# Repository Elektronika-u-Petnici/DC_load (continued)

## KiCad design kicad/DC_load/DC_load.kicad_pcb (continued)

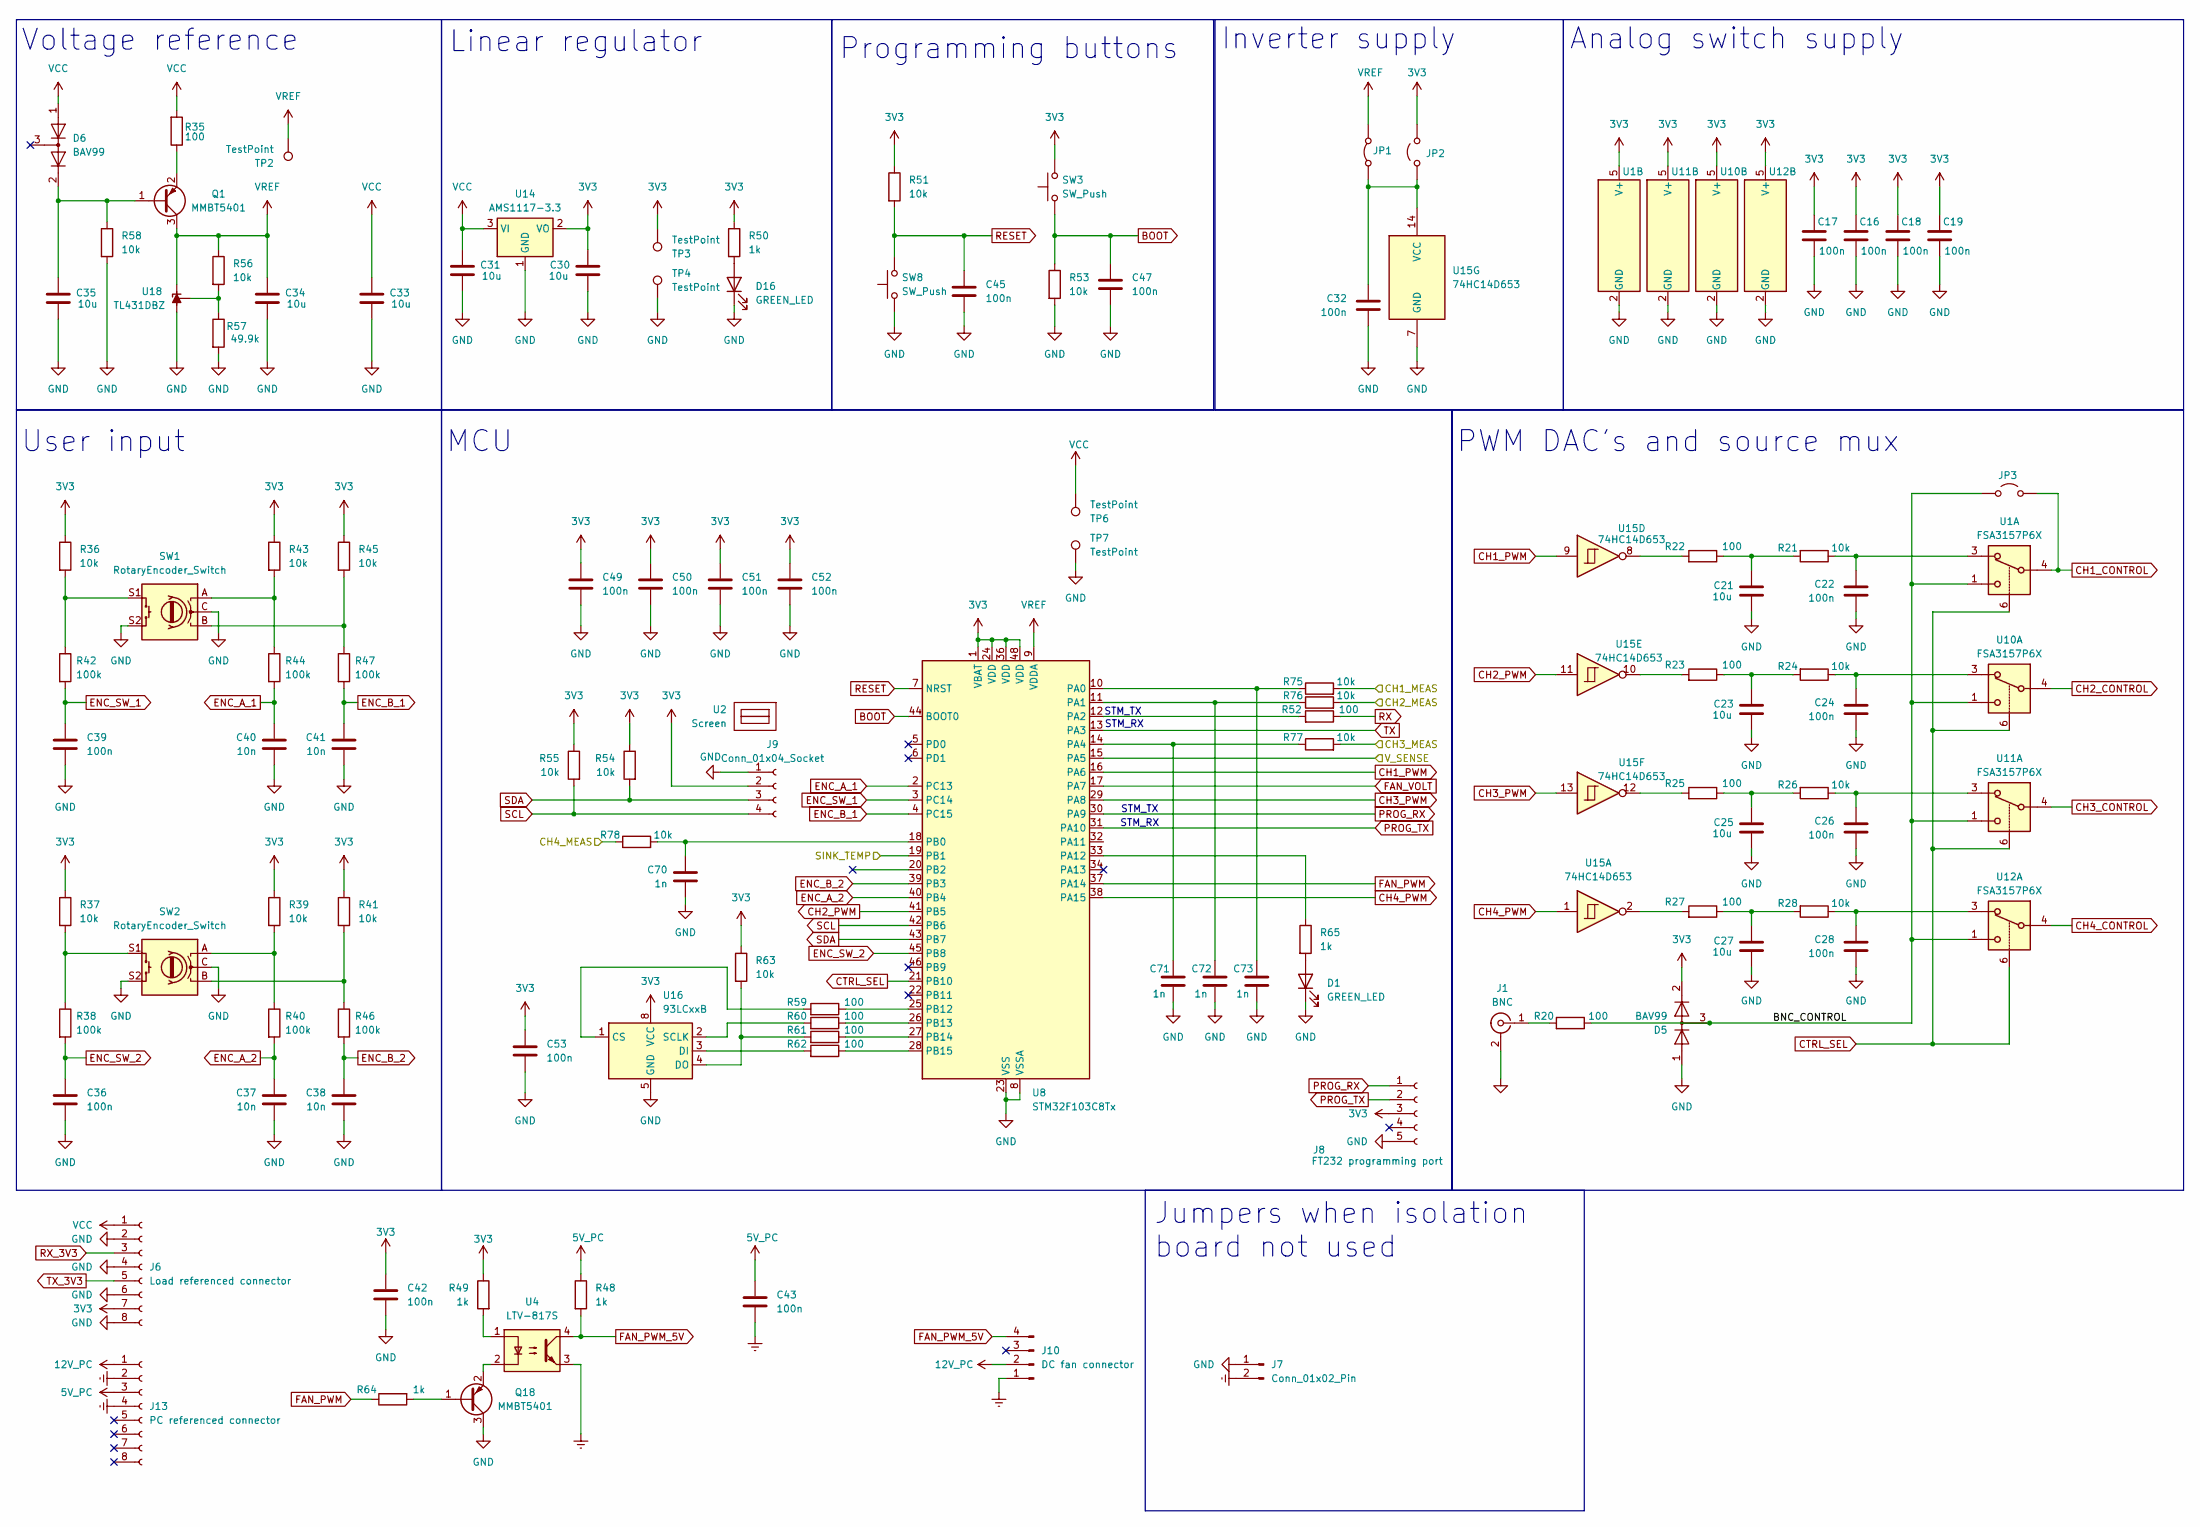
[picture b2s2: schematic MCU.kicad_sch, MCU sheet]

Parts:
C16, C17, C18, C19, C22, C24, C26, C28, C32, C36, C39, C42, C43, C45, C47, C49, C50, C51, C52, C53: 100n; C_0603_1608Metric_Pad1.08x0.95mm_HandSolder; LCSC C14663
C21, C23, C25, C27, C30, C31, C33, C34, C35: 10u; C_0603_1608Metric_Pad1.08x0.95mm_HandSolder; LCSC C96446
C37, C38, C40, C41: 10n; C_0603_1608Metric_Pad1.08x0.95mm_HandSolder; LCSC C57112
C70, C71, C72, C73: 1n; C_0603_1608Metric_Pad1.08x0.95mm_HandSolder; LCSC C1588
D1, D16: GREEN_LED; LED_0805_2012Metric_Pad1.15x1.40mm_HandSolder; LCSC C2297
D5, D6: BAV99; SOT-23; LCSC C2500
J1: BNC; BNC_Amphenol_B6252HB-NPP3G-50_Horizontal
J6: Load referenced connector; PinHeader_1x08_P2.54mm_Vertical
J7: Conn_01x02_Pin; PinHeader_1x02_P2.54mm_Vertical
J8: FT232 programming port; PinSocket_1x05_P2.54mm_Vertical
J9: Conn_01x04_Socket; PinSocket_1x04_P2.54mm_Vertical
J10: DC fan connector; PinHeader_1x04_P2.54mm_Vertical
J13: PC referenced connector; PinHeader_1x08_P2.54mm_Vertical
JP1: Jumper_2_Bridged; SolderJumper-2_P1.3mm_Bridged_RoundedPad1.0x1.5mm
JP2, JP3: Jumper_2_Open; SolderJumper-2_P1.3mm_Open_RoundedPad1.0x1.5mm
Q1, Q18: MMBT5401; SOT-23; LCSC C8326
R20, R22, R23, R25, R27, R35, R52, R59, R60, R61, R62: 100; R_0603_1608Metric_Pad0.98x0.95mm_HandSolder; LCSC C22775
R21, R24, R26, R28, R36, R37, R39, R41, R43, R45, R51, R53, R54, R55, R56, R58, R63, R75, R76, R77, R78: 10k; R_0603_1608Metric_Pad0.98x0.95mm_HandSolder; LCSC C25804
R38, R40, R42, R44, R46, R47: 100k; R_0603_1608Metric_Pad0.98x0.95mm_HandSolder; LCSC C25803
R48, R49, R64: 1k; R_0603_1608Metric_Pad0.98x0.95mm_HandSolder; LCSC C22962
R50, R65: 1k; R_0603_1608Metric_Pad0.98x0.95mm_HandSolder; LCSC C21190
R57: 49.9k; R_0603_1608Metric_Pad0.98x0.95mm_HandSolder; LCSC C23184
SW1, SW2: RotaryEncoder_Switch; RotaryEncoder_Alps_EC11E-Switch_Vertical_H20mm
SW3, SW8: SW_Push; TS-1088-AR02016; LCSC C720477
TP2, TP3, TP4, TP6, TP7: TestPoint; TestPoint_Pad_D2.0mm
U1, U10, U11, U12: FSA3157P6X; SOT-363_SC-70-6_Handsoldering
U2: Screen; WC1602A - below
U4: LTV-817S; SMDIP-4_W9.53mm
U8: STM32F103C8Tx; LQFP-48_7x7mm_P0.5mm
U14: AMS1117-3.3; SOT-223-3_TabPin2; LCSC C6186
U15: 74HC14D653; SOIC-14_3.9x8.7mm_P1.27mm; LCSC C5605
U16: 93LCxxB; SOIC-8_3.9x4.9mm_P1.27mm
U18: TL431DBZ; SOT-23; LCSC C3113

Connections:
3V3: C16.2, C17.2, C18.2, C19.2, C30.1, C42.2, C49.2, C50.2, C51.2, C52.2, C53.2, D5.2 (A), J6.7, J8.3, J9.2, JP2.2 (B), R36.1, R37.1, R39.1, R41.1, R43.1, R45.1, R49.1, R50.1, R51.1, R54.1, R55.1, R63.1, SW3.2, TP3.1, U1.5 (V+), U8.1 (VBAT), U8.24 (VDD), U8.36 (VDD), U8.48 (VDD), U10.5 (V+), U11.5 (V+), U12.5 (V+), U14.2 (VO), U16.8 (VCC); also elsewhere on the board
5V_PC: C43.2, J13.3, R48.1
12V_PC: J10.2, J13.1
/Microcontroller/BNC_CONTROL: D5.3 (K), JP3.1 (A), R20.1, U1.1, U10.1, U11.1, U12.1
/Microcontroller/CH1_MEAS: R75.2; also elsewhere on the board
/Microcontroller/CH2_MEAS: R76.2; also elsewhere on the board
/Microcontroller/CH3_MEAS: R77.2; also elsewhere on the board
/Microcontroller/CH4_MEAS: R78.1; also elsewhere on the board
/Microcontroller/SINK_TEMP: U8.19 (PB1); also elsewhere on the board
/Microcontroller/V_SENSE: U8.15 (PA5); also elsewhere on the board
BOOT: C47.2, R53.1, SW3.1, U8.44 (BOOT0)
CH1_CONTROL: JP3.2 (B), U1.4; also elsewhere on the board
CH1_PWM: U8.16 (PA6), U15.9
CH2_CONTROL: U10.4; also elsewhere on the board
CH2_PWM: U8.41 (PB5), U15.11
CH3_CONTROL: U11.4; also elsewhere on the board
CH3_PWM: U8.29 (PA8), U15.13
CH4_CONTROL: U12.4; also elsewhere on the board
CH4_PWM: U8.38 (PA15), U15.1
CTRL_SEL: U1.6, U8.21 (PB10), U10.6, U11.6, U12.6
ENC_A_1: C40.2, R44.2, U8.2 (PC13)
ENC_A_2: C37.2, R40.2, U8.40 (PB4)
ENC_B_1: C41.2, R47.2, U8.4 (PC15)
ENC_B_2: C38.2, R46.2, U8.39 (PB3)
ENC_SW_1: C39.2, R42.2, U8.3 (PC14)
ENC_SW_2: C36.2, R38.2, U8.45 (PB8)
Earth: C43.1, J7.2, J10.1, J13.2, J13.4, U4.3
FAN_PWM: R64.1, U8.37 (PA14)
FAN_PWM_5V: J10.4, R48.2, U4.4
FAN_VOLT: U8.17 (PA7)
GND: C16.1, C17.1, C18.1, C19.1, C21.2, C22.1, C23.2, C24.1, C25.2, C26.1, C27.2, C28.1, C30.2, C31.2, C32.1, C33.2, C34.2, C35.2, C36.1, C37.1, C38.1, C39.1, C40.1, C41.1, C42.1, C45.1, C47.1, C49.1, C50.1, C51.1, C52.1, C53.1, C70.1, C71.1, C72.1, C73.1, D1.1 (K), D5.1 (K), D16.1 (K), J1.2 (Ext), J6.2, J6.4, J6.6, J6.8, J7.1, J8.5, J9.1, Q18.3 (C), R53.2, R57.2, R58.2, SW1.C, SW1.S2, SW2.C, SW2.S2, SW8.1, TP4.1, TP7.1, U1.2 (GND), U8.8 (VSSA), U8.23 (VSS), U8.35 (VSS), U8.47 (VSS), U10.2 (GND), U11.2 (GND), U12.2 (GND), U14.1 (GND), U15.7 (GND), U16.5 (GND), U18.3 (A); also elsewhere on the board
unnamed: C21.1, R21.2, R22.1
unnamed: C22.2, R21.1, U1.3
unnamed: C23.1, R23.1, R24.2
unnamed: C24.2, R24.1, U10.3
unnamed: C25.1, R25.1, R26.2
unnamed: C26.2, R26.1, U11.3
unnamed: C27.1, R27.1, R28.2
unnamed: C28.2, R28.1, U12.3
unnamed: D1.2 (A), R65.2
unnamed: C35.1, D6.2 (A), Q1.1 (B), R58.1
unnamed: D16.2 (A), R50.2
unnamed: J1.1 (In), R20.2
unnamed: C32.2, JP1.1 (A), JP2.1 (A), U15.14 (VCC)
unnamed: Q1.2 (E), R35.1
unnamed: Q18.1 (B), R64.2
unnamed: Q18.2 (E), U4.2
unnamed: R22.2, U15.8
unnamed: R23.2, U15.10
unnamed: R25.2, U15.12
unnamed: R27.2, U15.2
unnamed: R36.2, R42.1, SW1.S1
unnamed: R37.2, R38.1, SW2.S1
unnamed: R39.2, R40.1, SW2.A
unnamed: R41.2, R46.1, SW2.B
unnamed: R43.2, R44.1, SW1.A
unnamed: R45.2, R47.1, SW1.B
unnamed: R49.2, U4.1
unnamed: C73.2, R75.1, U8.10 (PA0)
unnamed: C72.2, R76.1, U8.11 (PA1)
unnamed: R52.2, U8.12 (PA2)
unnamed: C71.2, R77.1, U8.14 (PA4)
unnamed: R65.1, U8.33 (PA12)
unnamed: C70.2, R78.2, U8.18 (PB0)
unnamed: R59.1, U8.25 (PB12)
unnamed: R60.1, U8.26 (PB13)
unnamed: R61.1, U8.27 (PB14)
unnamed: R62.1, U8.28 (PB15)
unnamed: R59.2, U16.1 (CS)
unnamed: R62.2, U16.3 (DI)
unnamed: R61.2, R63.2, U16.4 (DO)
unnamed: R60.2, U16.2 (SCLK)
unnamed: R56.2, R57.1, U18.2 (REF)
PROG_RX: J8.1, U8.30 (PA9)
PROG_TX: J8.2, U8.31 (PA10)
RESET: C45.2, R51.2, SW8.2, U8.7 (NRST)
RX: R52.1
RX_3V3: J6.3
SCL: J9.4, R55.2, U8.42 (PB6)
SDA: J9.3, R54.2, U8.43 (PB7)
TX: U8.13 (PA3)
TX_3V3: J6.5
VCC: C31.1, C33.1, D6.1 (K), J6.1, R35.2, TP6.1, U14.3 (VI); also elsewhere on the board
VREF: C34.1, JP1.2 (B), Q1.3 (C), R56.1, TP2.1, U8.9 (VDDA), U18.1 (K)

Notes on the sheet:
STM_RX
STM_TX
Programming buttons
Inverter supply
Jumpers when isolation board not used
PWM DAC's and source mux
Analog switch supply
MCU
Voltage reference
Linear regulator
User input

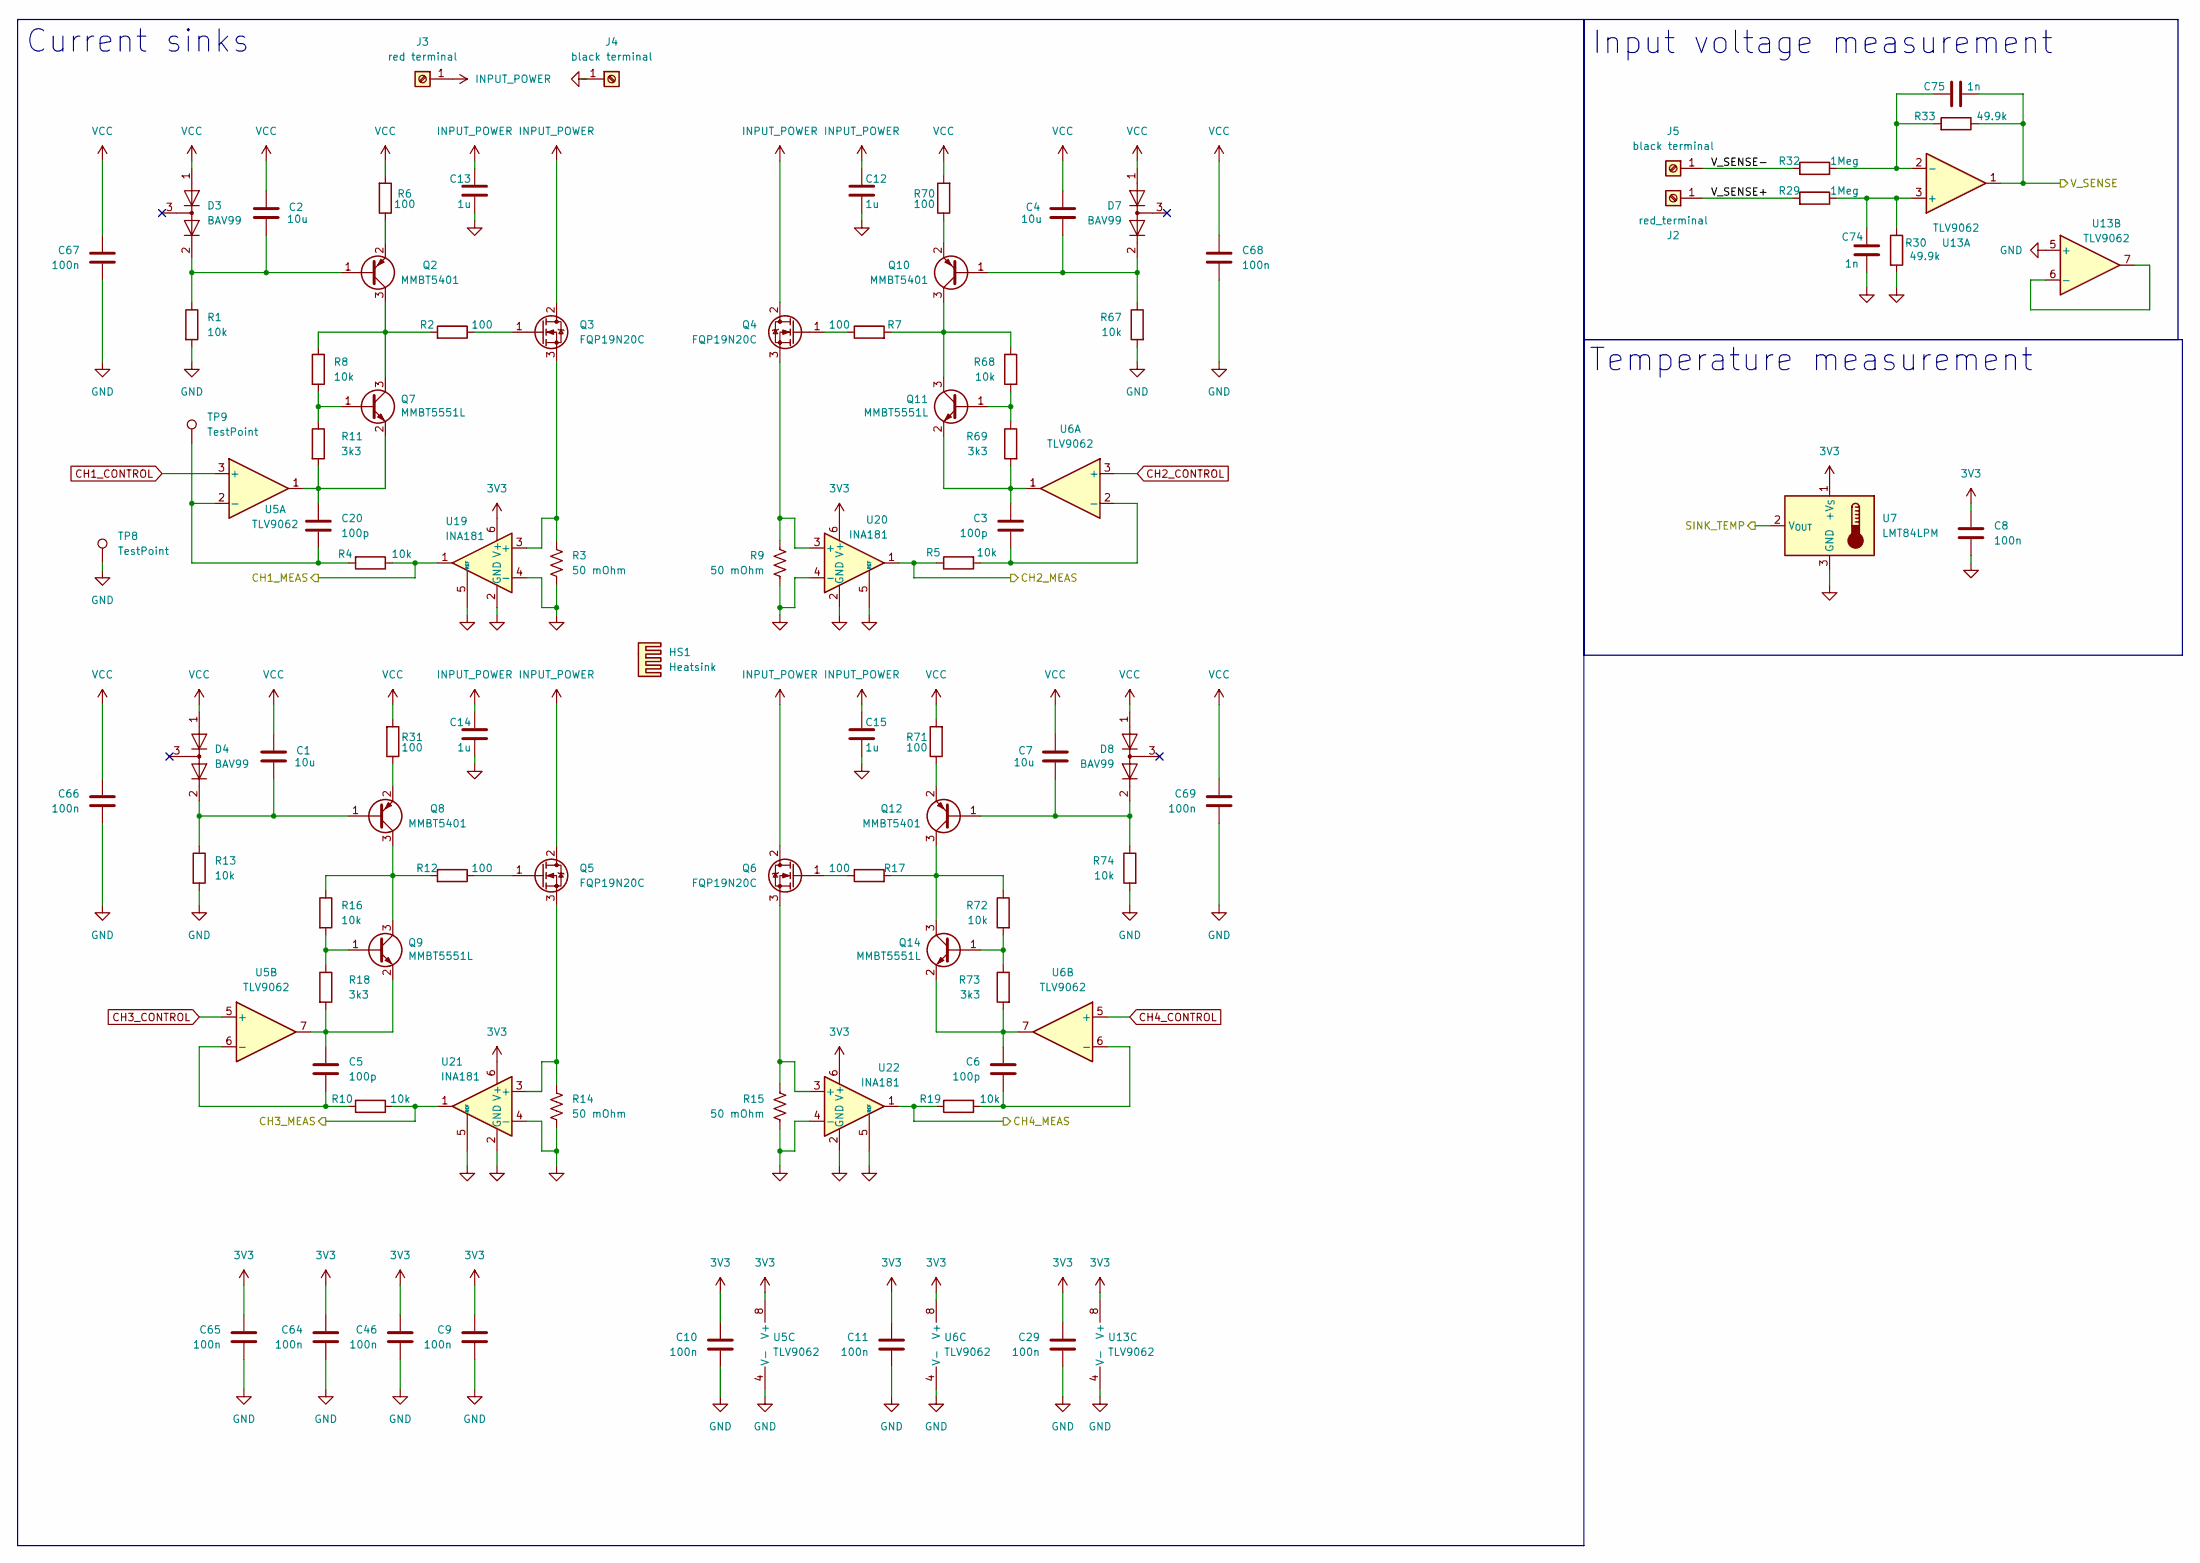
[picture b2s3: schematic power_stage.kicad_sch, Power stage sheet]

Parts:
C1, C2, C4, C7: 10u; C_0603_1608Metric_Pad1.08x0.95mm_HandSolder; LCSC C96446
C3, C5, C6, C20: 100p; C_0603_1608Metric_Pad1.08x0.95mm_HandSolder; LCSC C14858
C8: 100n; C_0603_1608Metric_Pad1.08x0.95mm_HandSolder
C9, C10, C11, C29, C46, C64, C65, C66, C67, C68, C69: 100n; C_0603_1608Metric_Pad1.08x0.95mm_HandSolder; LCSC C14663
C12, C13, C14, C15: 1u; C_2220_5750Metric_Pad1.97x5.40mm_HandSolder
C74, C75: 1n; C_0603_1608Metric_Pad1.08x0.95mm_HandSolder; LCSC C1588
D3, D4, D7, D8: BAV99; SOT-23; LCSC C2500
HS1: Heatsink; AMD_heatsink
J2: red_terminal; 4mm_terminal_red
J3: red terminal; 4mm_terminal_red
J4, J5: black terminal; 4mm_terminal_black
Q2, Q8, Q10, Q12: MMBT5401; SOT-23; LCSC C8326
Q3, Q4, Q5, Q6: FQP19N20C; TO-220-3_Horizontal_TabUp
Q7, Q9, Q11, Q14: MMBT5551L; SOT-23; LCSC C2145
R1, R4, R5, R8, R10, R13, R16, R19, R67, R68, R72, R74: 10k; R_0603_1608Metric_Pad0.98x0.95mm_HandSolder; LCSC C25804
R2, R6, R7, R12, R17, R31, R70, R71: 100; R_0603_1608Metric_Pad0.98x0.95mm_HandSolder; LCSC C22775
R3, R9, R14, R15: 50 mOhm; R_2512_6332Metric_Pad1.40x3.35mm_HandSolder
R11, R18, R69, R73: 3k3; R_0603_1608Metric_Pad0.98x0.95mm_HandSolder; LCSC C22978
R29, R32: 1Meg; R_0603_1608Metric_Pad0.98x0.95mm_HandSolder; LCSC C22935
R30, R33: 49.9k; R_0603_1608Metric_Pad0.98x0.95mm_HandSolder; LCSC C23184
TP8, TP9: TestPoint; TestPoint_Pad_D2.0mm
U5, U6, U13: TLV9062; SOIC-8_3.9x4.9mm_P1.27mm
U7: LMT84LPM; TO-92_Inline_W4.0mm_Horizontal_FlatSideUp
U19, U20, U21, U22: INA181; SOT-23-6

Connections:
3V3: C8.1, C9.2, C10.2, C11.2, C29.2, C46.2, C64.2, C65.2, U5.8 (V+), U6.8 (V+), U7.1 (+V_{S}), U13.8 (V+), U19.6 (V+), U20.6 (V+), U21.6 (V+), U22.6 (V+); also elsewhere on the board
/Microcontroller/CH1_MEAS: R4.1, U19.1; also elsewhere on the board
/Microcontroller/CH2_MEAS: R5.1, U20.1; also elsewhere on the board
/Microcontroller/CH3_MEAS: R10.1, U21.1; also elsewhere on the board
/Microcontroller/CH4_MEAS: R19.1, U22.1; also elsewhere on the board
/Microcontroller/SINK_TEMP: U7.2 (V_{OUT}); also elsewhere on the board
/Microcontroller/V_SENSE: C75.1, R33.1, U13.1; also elsewhere on the board
/Power_stage/V_SENSE+: J2.1, R29.2
/Power_stage/V_SENSE-: J5.1, R32.2
CH1_CONTROL: U5.3 (+); also elsewhere on the board
CH2_CONTROL: U6.3 (+); also elsewhere on the board
CH3_CONTROL: U5.5 (+); also elsewhere on the board
CH4_CONTROL: U6.5 (+); also elsewhere on the board
GND: C8.2, C9.1, C10.1, C11.1, C12.2, C13.2, C14.2, C15.2, C29.1, C46.1, C64.1, C65.1, C66.1, C67.1, C68.1, C69.1, C74.1, J4.1, R1.2, R3.2, R9.2, R13.2, R14.2, R15.2, R30.2, R67.2, R74.2, TP8.1, U5.4 (V-), U6.4 (V-), U7.3 (GND), U13.4 (V-), U13.5 (+), U19.2 (GND), U19.4 (-), U19.5 (REF), U20.2 (GND), U20.4 (-), U20.5 (REF), U21.2 (GND), U21.4 (-), U21.5 (REF), U22.2 (GND), U22.4 (-), U22.5 (REF); also elsewhere on the board
INPUT_POWER: C12.1, C13.1, C14.1, C15.1, J3.1, Q3.2 (D), Q4.2 (D), Q5.2 (D), Q6.2 (D)
unnamed: C2.2, D3.2 (A), Q2.1 (B), R1.1
unnamed: C1.2, D4.2 (A), Q8.1 (B), R13.1
unnamed: C4.2, D7.2 (A), Q10.1 (B), R67.1
unnamed: C7.2, D8.2 (A), Q12.1 (B), R74.1
unnamed: Q2.3 (C), Q7.3 (C), R2.2, R8.1
unnamed: Q2.2 (E), R6.1
unnamed: Q3.1 (G), R2.1
unnamed: Q3.3 (S), R3.1, U19.3 (+)
unnamed: Q4.1 (G), R7.1
unnamed: Q4.3 (S), R9.1, U20.3 (+)
unnamed: Q5.1 (G), R12.1
unnamed: Q5.3 (S), R14.1, U21.3 (+)
unnamed: Q6.1 (G), R17.1
unnamed: Q6.3 (S), R15.1, U22.3 (+)
unnamed: Q7.1 (B), R8.2, R11.1
unnamed: C20.2, Q7.2 (E), R11.2, U5.1
unnamed: Q8.3 (C), Q9.3 (C), R12.2, R16.1
unnamed: Q8.2 (E), R31.1
unnamed: Q9.1 (B), R16.2, R18.1
unnamed: C5.2, Q9.2 (E), R18.2, U5.7
unnamed: Q10.3 (C), Q11.3 (C), R7.2, R68.1
unnamed: Q10.2 (E), R70.1
unnamed: Q11.1 (B), R68.2, R69.1
unnamed: C3.2, Q11.2 (E), R69.2, U6.1
unnamed: Q12.3 (C), Q14.3 (C), R17.2, R72.1
unnamed: Q12.2 (E), R71.1
unnamed: Q14.1 (B), R72.2, R73.1
unnamed: C6.2, Q14.2 (E), R73.2, U6.7
unnamed: C20.1, R4.2, TP9.1, U5.2 (-)
unnamed: C5.1, R10.2, U5.6 (-)
unnamed: C3.1, R5.2, U6.2 (-)
unnamed: C6.1, R19.2, U6.6 (-)
unnamed: C74.2, R29.1, R30.1, U13.3 (+)
unnamed: C75.2, R32.1, R33.2, U13.2 (-)
unnamed: U13.6 (-), U13.7
VCC: C1.1, C2.1, C4.1, C7.1, C66.2, C67.2, C68.2, C69.2, D3.1 (K), D4.1 (K), D7.1 (K), D8.1 (K), R6.2, R31.2, R70.2, R71.2; also elsewhere on the board

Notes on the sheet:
Input voltage measurement
Current sinks
Temperature measurement

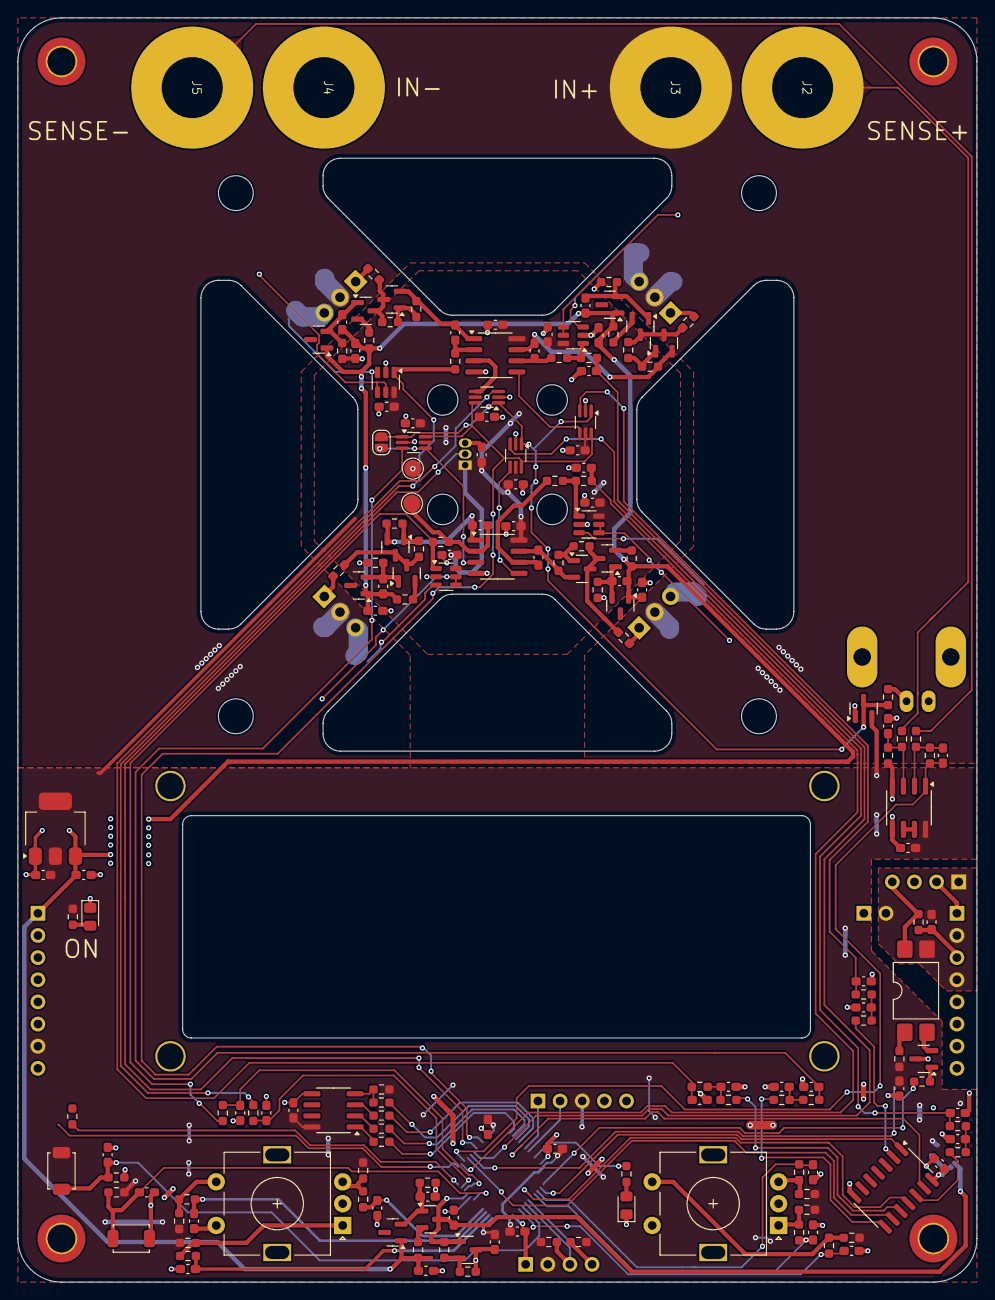
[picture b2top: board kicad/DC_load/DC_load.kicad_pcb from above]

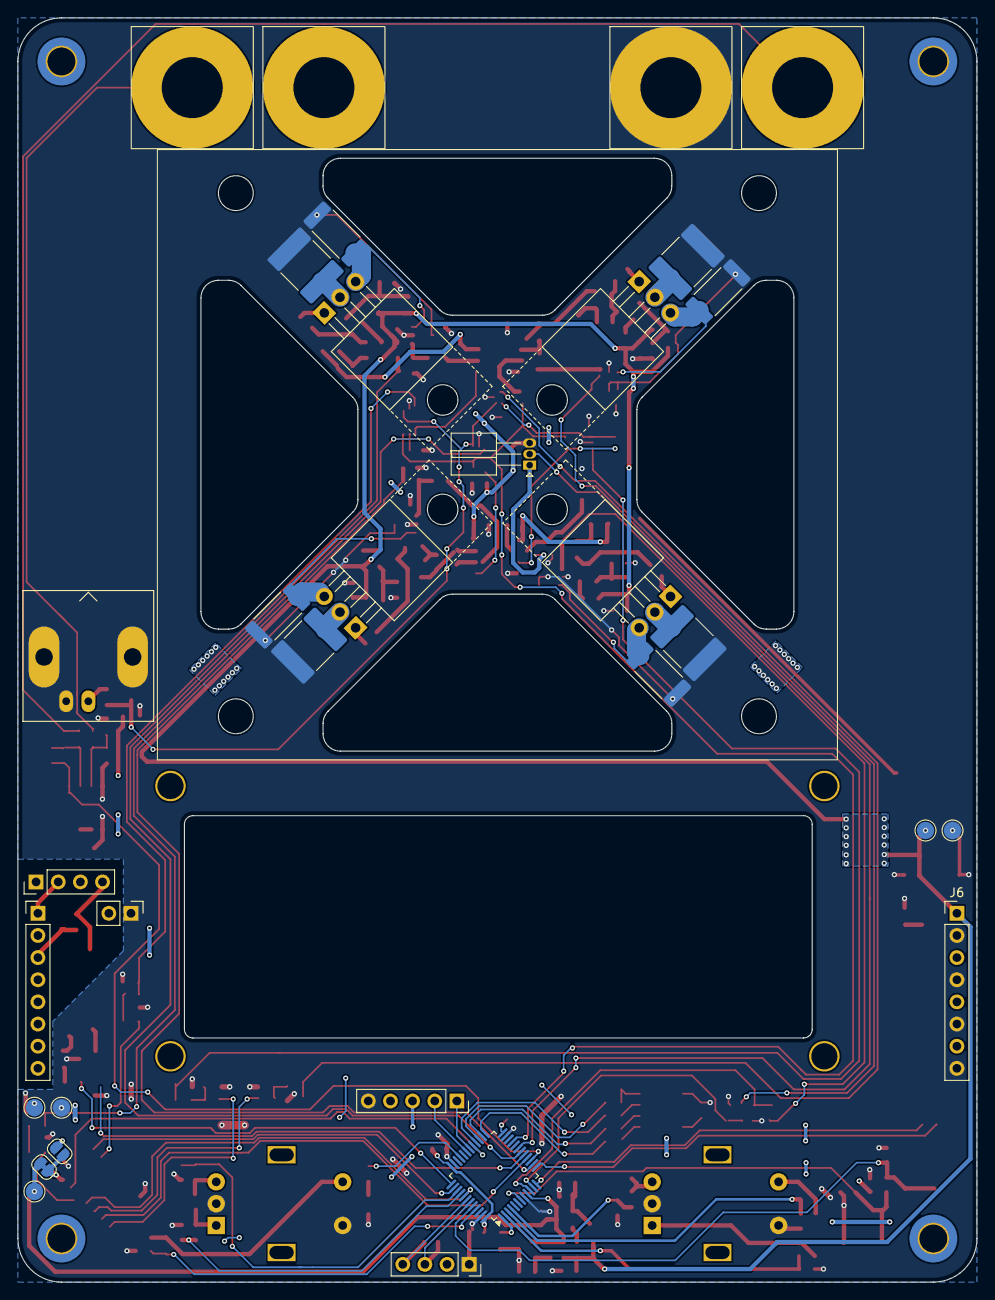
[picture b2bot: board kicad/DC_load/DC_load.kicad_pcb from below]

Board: 2 copper layers, 110.0 x 145.0 mm, 210 parts (32 on the bottom side), 117 nets.

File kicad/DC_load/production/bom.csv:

Designator,Footprint,Quantity,Value,LCSC Part #
"C1, C2, C21, C23, C25, C27, C30, C31, C33, C34, C35, C4, C54, C56, C57, C58, C59, C60, C61, C62, C63, C7",0603,22,10u,C96446
"C10, C11, C16, C17, C18, C19, C22, C24, C26, C28, C29, C32, C36, C39, C45, C46, C47, C48, C49, C50, C51, C52, C53, C55, C64, C65, C66, C67, C68, C69, C9",0603,31,100n,C14663
"C12, C13, C14, C15",2220,4,1u,
"C20, C3, C5, C6",0603,4,100p,C14858
"C37, C38, C40, C41, C44",0603,5,10n,C57112
"C42, C43",0603,2,47p,C1671
"C70, C71, C72, C73, C74, C75",0603,6,1n,C1588
C8,0603,1,100n,
"D1, D2",D_SOD-123,2,1N4148W,
"D3, D4, D6, D7, D8",SOT-23,5,BAV99,C2500
D5,D_SOD-323,1,1N5819WS,C191023
HS1,AMD_heatsink,1,Heatsink,
J1,BNC_Amphenol_B6252HB-NPP3G-50_Horizontal,1,BNC,
J10,PinHeader_1x04_P2.54mm_Vertical,1,DC fan connector,
J2,4mm_terminal_red,1,red_terminal,
J3,4mm_terminal_red,1,red terminal,
"J4, J5",4mm_terminal_black,2,black terminal,
J6,62910416121,1,USB_B,
J8,PinSocket_1x05_P2.54mm_Vertical,1,FT232 programming port,
J9,PinSocket_1x04_P2.54mm_Vertical,1,Conn_01x04_Socket,
JP1,SolderJumper-2_P1.3mm_Bridged_RoundedPad1.0x1.5mm,1,Jumper_2_Bridged,
"JP2, JP3",SolderJumper-2_P1.3mm_Open_RoundedPad1.0x1.5mm,2,Jumper_2_Open,
L4,L_Bourns_SRN6045TA,1,4.7u,
"Q1, Q10, Q12, Q2, Q8",SOT-23,5,MMBT5401,C8326
"Q11, Q14, Q7, Q9",SOT-23,4,MMBT5551L,C2145
Q13,SOT-23,1,AO3400A,C20917
"Q3, Q4, Q5, Q6",TO-220-3_Horizontal_TabUp,4,FQP19N20C,
"R1, R10, R13, R16, R19, R21, R24, R26, R28, R36, R37, R39, R4, R41, R43, R45, R5, R51, R53, R54, R55, R56, R58, R63, R64, R65, R67, R68, R72, R74, R75, R76, R77, R78, R8",0603,35,10k,C25804
"R11, R18, R69, R73",0603,4,3k3,C22978
"R12, R17, R2, R20, R22, R23, R25, R27, R31, R34, R35, R50, R52, R59, R6, R60, R61, R62, R7, R70, R71",0603,21,100,C22775
"R14, R15, R3, R9",2512,4,50 mOhm,
"R29, R32",0603,2,1Meg,C22935
"R30, R33, R57, R66",0603,4,49.9k,C23184
"R38, R40, R42, R44, R46, R47",0603,6,100k,C25803
"R48, R49",0603,2,22,C23345
"SW1, SW2",RotaryEncoder_Alps_EC11E-Switch_Vertical_H20mm,2,RotaryEncoder_Switch,
"SW3, SW8",SW_TH_Tactile_Omron_B3F-10xx,2,SW_Push,
"TP1, TP2, TP3, TP4, TP5, TP6, TP7, TP8, TP9",TestPoint_Pad_D2.0mm,9,TestPoint,
"U1, U10, U11, U12",SOT-363_SC-70-6_Handsoldering,4,FSA3157P6X,
"U13, U5, U6",SOIC-8_3.9x4.9mm_P1.27mm,3,TLV9062,
U14,SOT-223-3_TabPin2,1,AMS1117-3.3,C6186
U15,SOIC-14_3.9x8.7mm_P1.27mm,1,74HC14D653,C5605
U16,SOIC-8_3.9x4.9mm_P1.27mm,1,93LCxxB,
U17,SOIC-16_3.9x9.9mm_P1.27mm,1,CH340C,
U18,SOT-23,1,TL431DBZ,C3113
"U19, U20, U21, U22",SOT-23-6,4,INA181,
U2,WC1602A - below,1,Screen,
U7,TO-92_Inline_W4.0mm_Horizontal_FlatSideUp,1,LMT84LPM,
U8,LQFP-48_7x7mm_P0.5mm,1,STM32F103C8Tx,
